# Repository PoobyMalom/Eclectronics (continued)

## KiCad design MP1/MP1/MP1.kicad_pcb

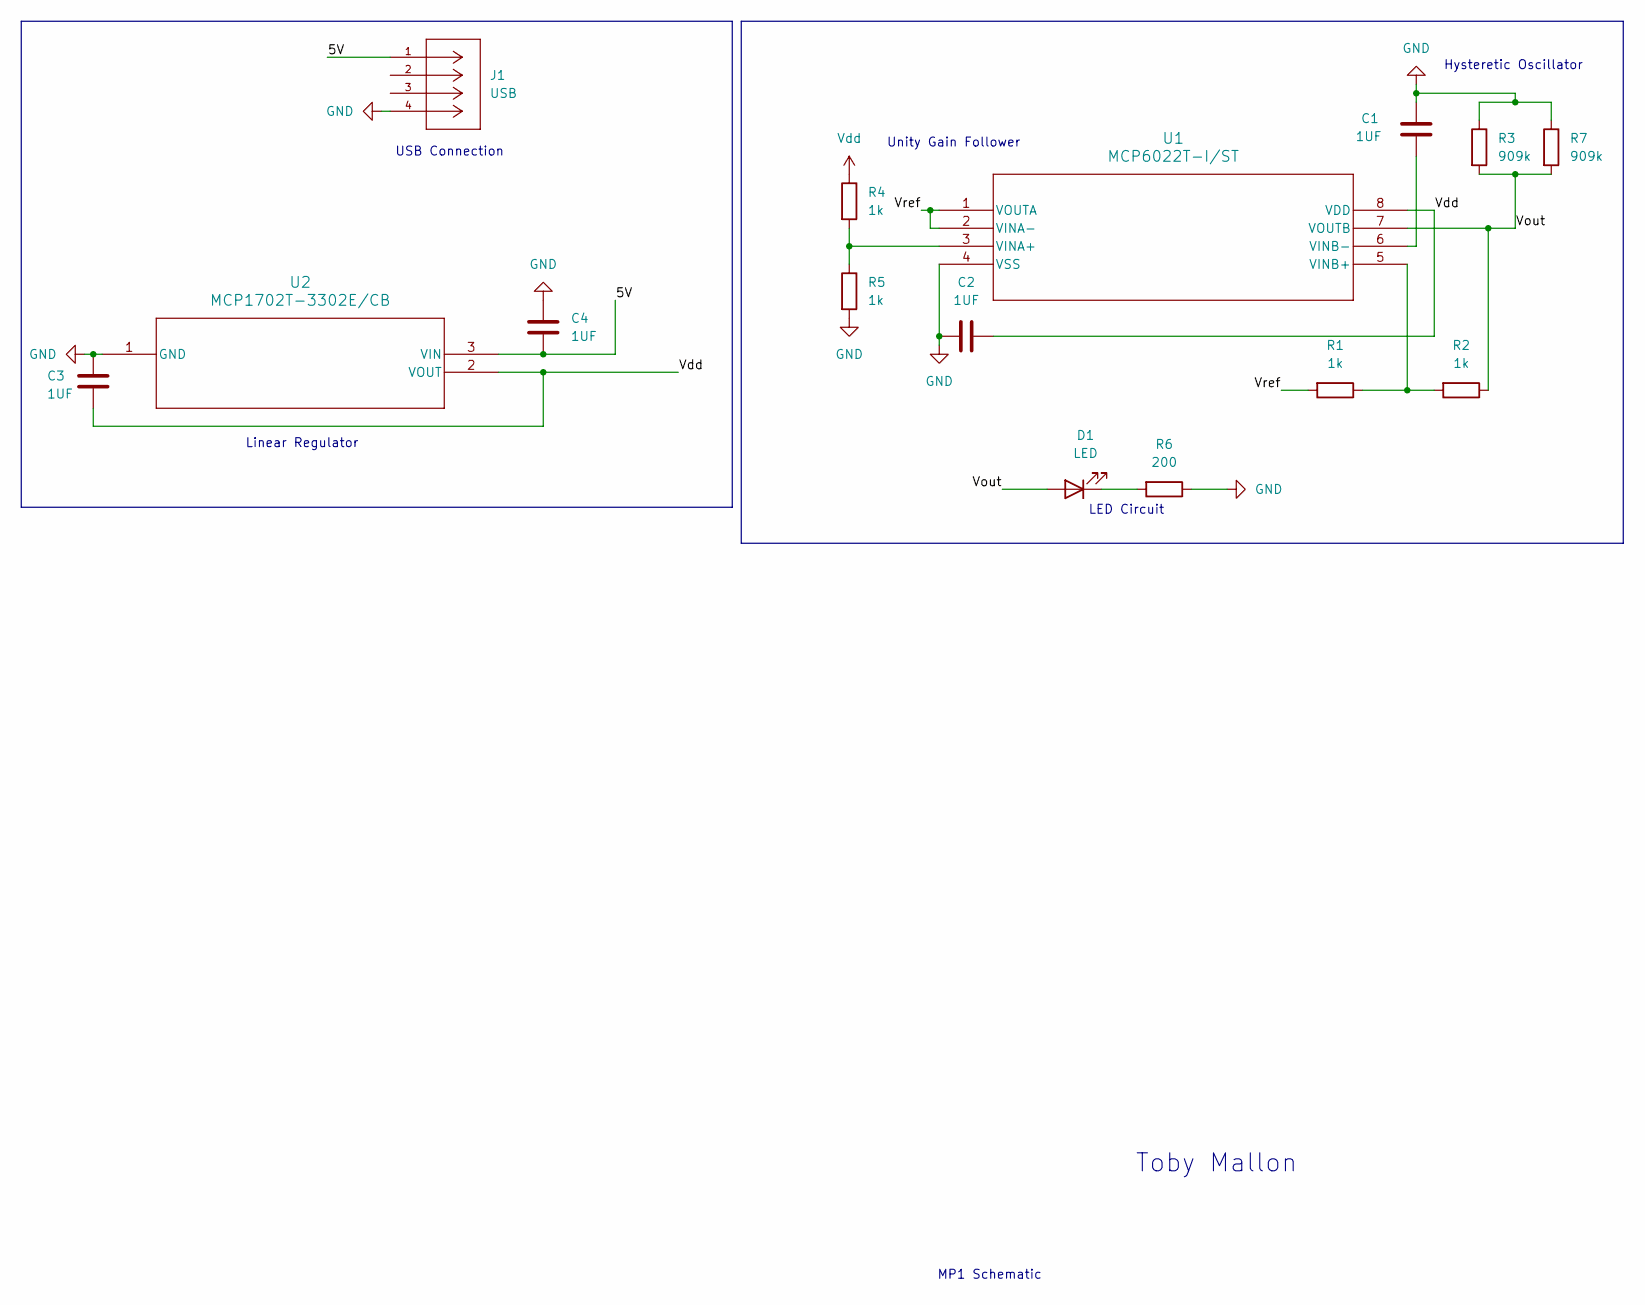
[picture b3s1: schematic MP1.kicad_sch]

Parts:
C1, C2, C3, C4: 1UF; CAPC17595_95N_KEM
D1: LED; LED_LTST-C171_LTO
J1: USB; CONN_480370001_MOL; MANUFACTURER_PART_NUMBER 480370001
R1, R2, R4, R5: 1k; RC0603N_YAG
R3, R7: 909k; RC0603N_YAG
R6: 200; RC0603N_YAG
U1: MCP6022T-I/ST; TSSOP8_MC_MCH
U2: MCP1702T-3302E/CB; SOT-23A_MC_MCH

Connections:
/5V: C4.2, J1.1, U2.3 (VIN)
/Vout: D1.2 (A), R2.1, R3.2, R7.2, U1.7 (VOUTB)
/Vref: R1.2, U1.1 (VOUTA), U1.2 (VINA-)
GND: C1.1, C2.2, C3.1, C4.1, J1.4, R3.1, R5.2, R6.1, R7.1, U1.4 (VSS), U2.1 (GND)
unnamed: D1.1 (K), R6.2
unnamed: R4.2, R5.1, U1.3 (VINA+)
unnamed: R1.1, R2.2, U1.5 (VINB+)
unnamed: C1.2, U1.6 (VINB-)
Vdd: C2.1, C3.2, R4.1, U1.8 (VDD), U2.2 (VOUT)

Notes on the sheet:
Hysteretic Oscillator
Unity Gain Follower
LED Circuit
Toby Mallon
MP1 Schematic
USB Connection
Linear Regulator

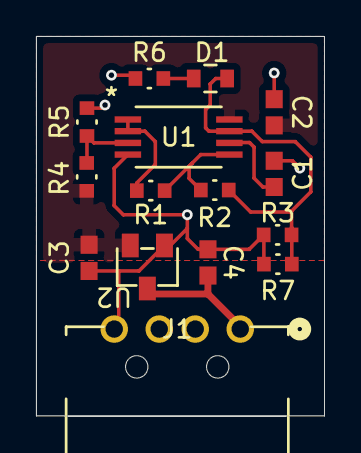
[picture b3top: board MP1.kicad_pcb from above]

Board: 2 copper layers, 16.0 x 21.1 mm, 15 parts (0 on the bottom side), 9 nets.
